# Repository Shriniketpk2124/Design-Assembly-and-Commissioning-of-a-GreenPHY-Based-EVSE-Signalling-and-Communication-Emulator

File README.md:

# Design, Assembly and Commissioning of a GreenPHY-Based EVSE Signalling and Communication Emulator

> **New here?** Start with [the software quickstart](docs/SOFTWARE_QUICKSTART.md) — two ways to fire up the JoSEV SECC (real hardware, or a two-container software simulation).

This repository documents an engineering prototype for EVSE-side control-pilot
(CP) signalling, HomePlug Green PHY communication and ISO 15118 message
observation with a real electric vehicle.

The project combines a custom mixed-signal PCB, an Arduino Nano, a Raspberry
Pi, a Devolo Green PHY modem and a hardware-adapted EcoG `iso15118` SECC.

> [!CAUTION]
> This is a laboratory communication emulator, not a charger. It has no
> authorized high-voltage DC source, verified insulation-monitoring system,
> pre-charge power stage or energy-transfer path. Never connect an HV/DC source
> or use this project to charge a vehicle.

## Demonstrated scope

The validated setup demonstrated:

- IEC 61851 CP generation and feedback monitoring;
- 1 kHz CP PWM, including the 5% HLC duty cycle;
- EV detection through the CP resistor states;
- EVSE-side SLAC using the `plc-utils` `evse` process;
- IPv6 link-local communication and SDP;
- ISO 15118-2 application-message exchange with external payment and no TLS;
- controlled termination before any physical energy transfer.

The final communication experiment used an explicitly enabled, protocol-only
PreCharge probe. It emulated the protocol status needed to pass CableCheck,
reached `PreChargeReq`, rejected the requested voltage/current command and
latched an external STOP. No DC output was produced.

## Repository layout

| Path | Contents |
| --- | --- |
| `hardware/kicad/PWM_Schematic/` | KiCad schematic, PCB, project-local symbols and footprints, and ERC/DRC reports |
| `hardware/bom/` | Bill of materials exported from the final schematic |
| `software/arduino/` | Arduino Nano CP controller and feedback-monitor firmware |
| `software/raspberry-pi/` | Raspberry Pi console, cockpit, test-day and evidence-collection tools |
| `software/josev-modifications/` | Hardware-controller additions for the EcoG ISO 15118 SECC |
| `software/configuration/` | Public configuration templates without local identifiers or secrets |
| `validation/procedures/` | Bench and real-EV validation procedures |
| `validation/selected-results/` | Sanitized results selected for publication |
| `thesis/` | Publication status only; the thesis report is not distributed here |

Raw packet captures, complete run folders, local environment files, vehicle
identifiers and PLC network keys are intentionally excluded.

## System overview

1. The Arduino generates the CP waveform and publishes comparator feedback over
   a serial connection.
2. The Raspberry Pi console is the sole owner of the Arduino serial connection
   and the two CP-path relay GPIOs.
3. The console writes an atomic state snapshot under `/run/evse-monday`.
4. The modified SECC reads that snapshot instead of controlling serial or GPIO
   hardware from inside the container.
5. The `plc-utils` `evse` process is the sole EVSE-side SLAC owner.
6. The Devolo modem carries HomePlug Green PHY traffic between the PCB coupling
   network and the vehicle.
7. The operations script records packet captures, application logs, controller
   state and checksums for each test attempt.

The word **Monday** remains in several tested script, class and configuration
names. It was the internal name of the final real-EV test workflow; it is not a
separate product or protocol.

## Hardware interface

The final KiCad PCB assigns the four-position vehicle-interface terminal as:

| Terminal | Net |
| --- | --- |
| `J2.1` | `EVSE_CP_OUT` |
| `J2.2` | `EVSE_PP_OUT` |
| `J2.3` | `ISO_GND` |
| `J2.4` | Not connected |

Verify these assignments against the supplied schematic and PCB before making
any physical connection. Wiring changes must be performed with all power
removed.

## Software provenance

The Josev modifications were developed against:

- upstream repository: `https://github.com/EcoG-io/iso15118.git`
- recorded base commit: `76bf85be572d16adbcd009a985d605622c3b7227`

The repository contains the project-specific additions and operational files,
not a claim of ownership over the upstream project. Retain all upstream license
and attribution notices when constructing a working tree.

## Replication order

This project is not a one-command charger build. A new user should proceed in
the following order:

1. Read this README and the safety limits.
2. Open `hardware/kicad/PWM_Schematic/PWM_Schematic.kicad_pro` and inspect the
   schematic, PCB, connector assignments and ERC/DRC reports.
3. Review the BOM and confirm every fitted component and polarity against the
   physical assembly.
4. Compile the Arduino sketch in `software/arduino/evse_cp_feedback_led/` for an
   Arduino Nano. The final sketch was verified with Arduino IDE and used 6102
   bytes of program storage and 448 bytes of global SRAM.
5. Prepare a Raspberry Pi with Docker Compose, Python 3, `tmux`, `tcpdump`,
   `plc-utils` and the required GPIO/serial permissions.
6. Follow the [Raspberry Pi installation and first-start guide](software/raspberry-pi/README.md)
   to check out the recorded upstream `iso15118` revision, prepare the local
   configuration and install the project additions.
7. Copy the public templates from `software/configuration/` to local,
   git-ignored configuration files and replace every `CHANGE_ME` value.
8. Run the hardware-independent tests and the operations-script preflight.
9. Validate State A, State B and 5% HLC feedback using bench loads before a
   vehicle is connected.
10. Only after the bench checks pass, follow the hardware-specific procedure in
    `validation/procedures/REAL_EV_COMMUNICATION_TEST_RUNBOOK.md`.

## Operating modes

`MONDAY_PRECHARGE_PROBE` materially changes the protocol boundary:

| Value | Behaviour |
| --- | --- |
| `0` | Default fail-safe mode. Reports `No_IMD`/`EVSE_NotReady` and requests STOP when CableCheck cannot be truthfully completed. |
| `1` | Test-only protocol probe. Emulates CableCheck readiness to observe entry into PreCharge, but still blocks the requested charging command and requests STOP. |

The probe does not add an IMD, contactor, pre-charge circuit or voltage source.
Do not enable it on a system containing an HV/DC energy path.

## Evidence and privacy

Complete test archives can contain MAC addresses, PLC network keys, EVCC
identifiers, hostnames, operator names and packet payloads. They are private
laboratory evidence and are not suitable for direct publication. Publish only
purpose-selected, sanitized extracts.

## Project status

The repository captures a thesis prototype and its validated laboratory
workflow. It is intended for research, review and reproducibility work by
qualified users. It is not production EVSE firmware and has not been certified
for charging, electrical safety or standards conformance.

The thesis report is withheld until publication permission is confirmed.

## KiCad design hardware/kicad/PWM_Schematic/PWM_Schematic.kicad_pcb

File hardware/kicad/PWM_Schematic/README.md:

\# PWM and Control-Pilot PCB

This directory contains the KiCad source files for the mixed-signal PCB used by

the Green PHY EVSE signalling and communication emulator.

\## Requirements

\- KiCad 10

\- Standard KiCad symbol libraries

\- Standard KiCad footprint libraries

\- Standard KiCad 3D-model package, if 3D rendering is required

\## Opening the project

Open:

`PWM\_Schematic.kicad\_pro`

The custom symbol and footprint libraries required by the project are included

locally in the `symbols/` and `footprints/` directories. The corresponding

`sym-lib-table` and `fp-lib-table` files use `${KIPRJMOD}` paths, so the project

does not depend on machine-specific directories.

\## Included source files

\- `PWM\_Schematic.kicad\_pro` — KiCad project settings

\- `PWM\_Schematic.kicad\_sch` — schematic

\- `PWM\_Schematic.kicad\_pcb` — PCB layout

\- `PWM\_Schematic.kicad\_dru` — custom design rules

\- `symbols/` — project-local custom symbols

\- `footprints/` — project-local custom footprints

\- `reports/` — final ERC and DRC reports

\## Verification status

Final verification performed on 2026-10-04:

\- ERC errors: 0

\- ERC warnings: 0

\- DRC violations: 0

\- Unconnected pads: 0

\- Footprint errors: 0

The corresponding reports are stored in `reports/`.

\## 3D models

Standard components use the official KiCad 10 3D-model library where available.

Nonportable or incorrect custom 3D-model references were removed. Missing custom

3D models do not affect schematic connectivity, PCB routing, fabrication output

or design-rule verification.

\## Fabrication outputs

Historical Gerber and Aisler exports are not included because they predate the

final DRC-clean source revision. Fabrication outputs should be regenerated from

the checked PCB source when required.

\## Scope and safety

This PCB is a research prototype for control-pilot signalling, proximity-pilot

interfacing and communication-layer experimentation. It is not a certified EVSE

power stage and must not be treated as authorization for high-voltage or energy

transfer.

\## Third-party library data

Some project-local symbol and footprint definitions originated from manufacturer

or electronic-library-loader data and were adapted for this project. Applicable

redistribution terms must be reviewed before making the repository public.

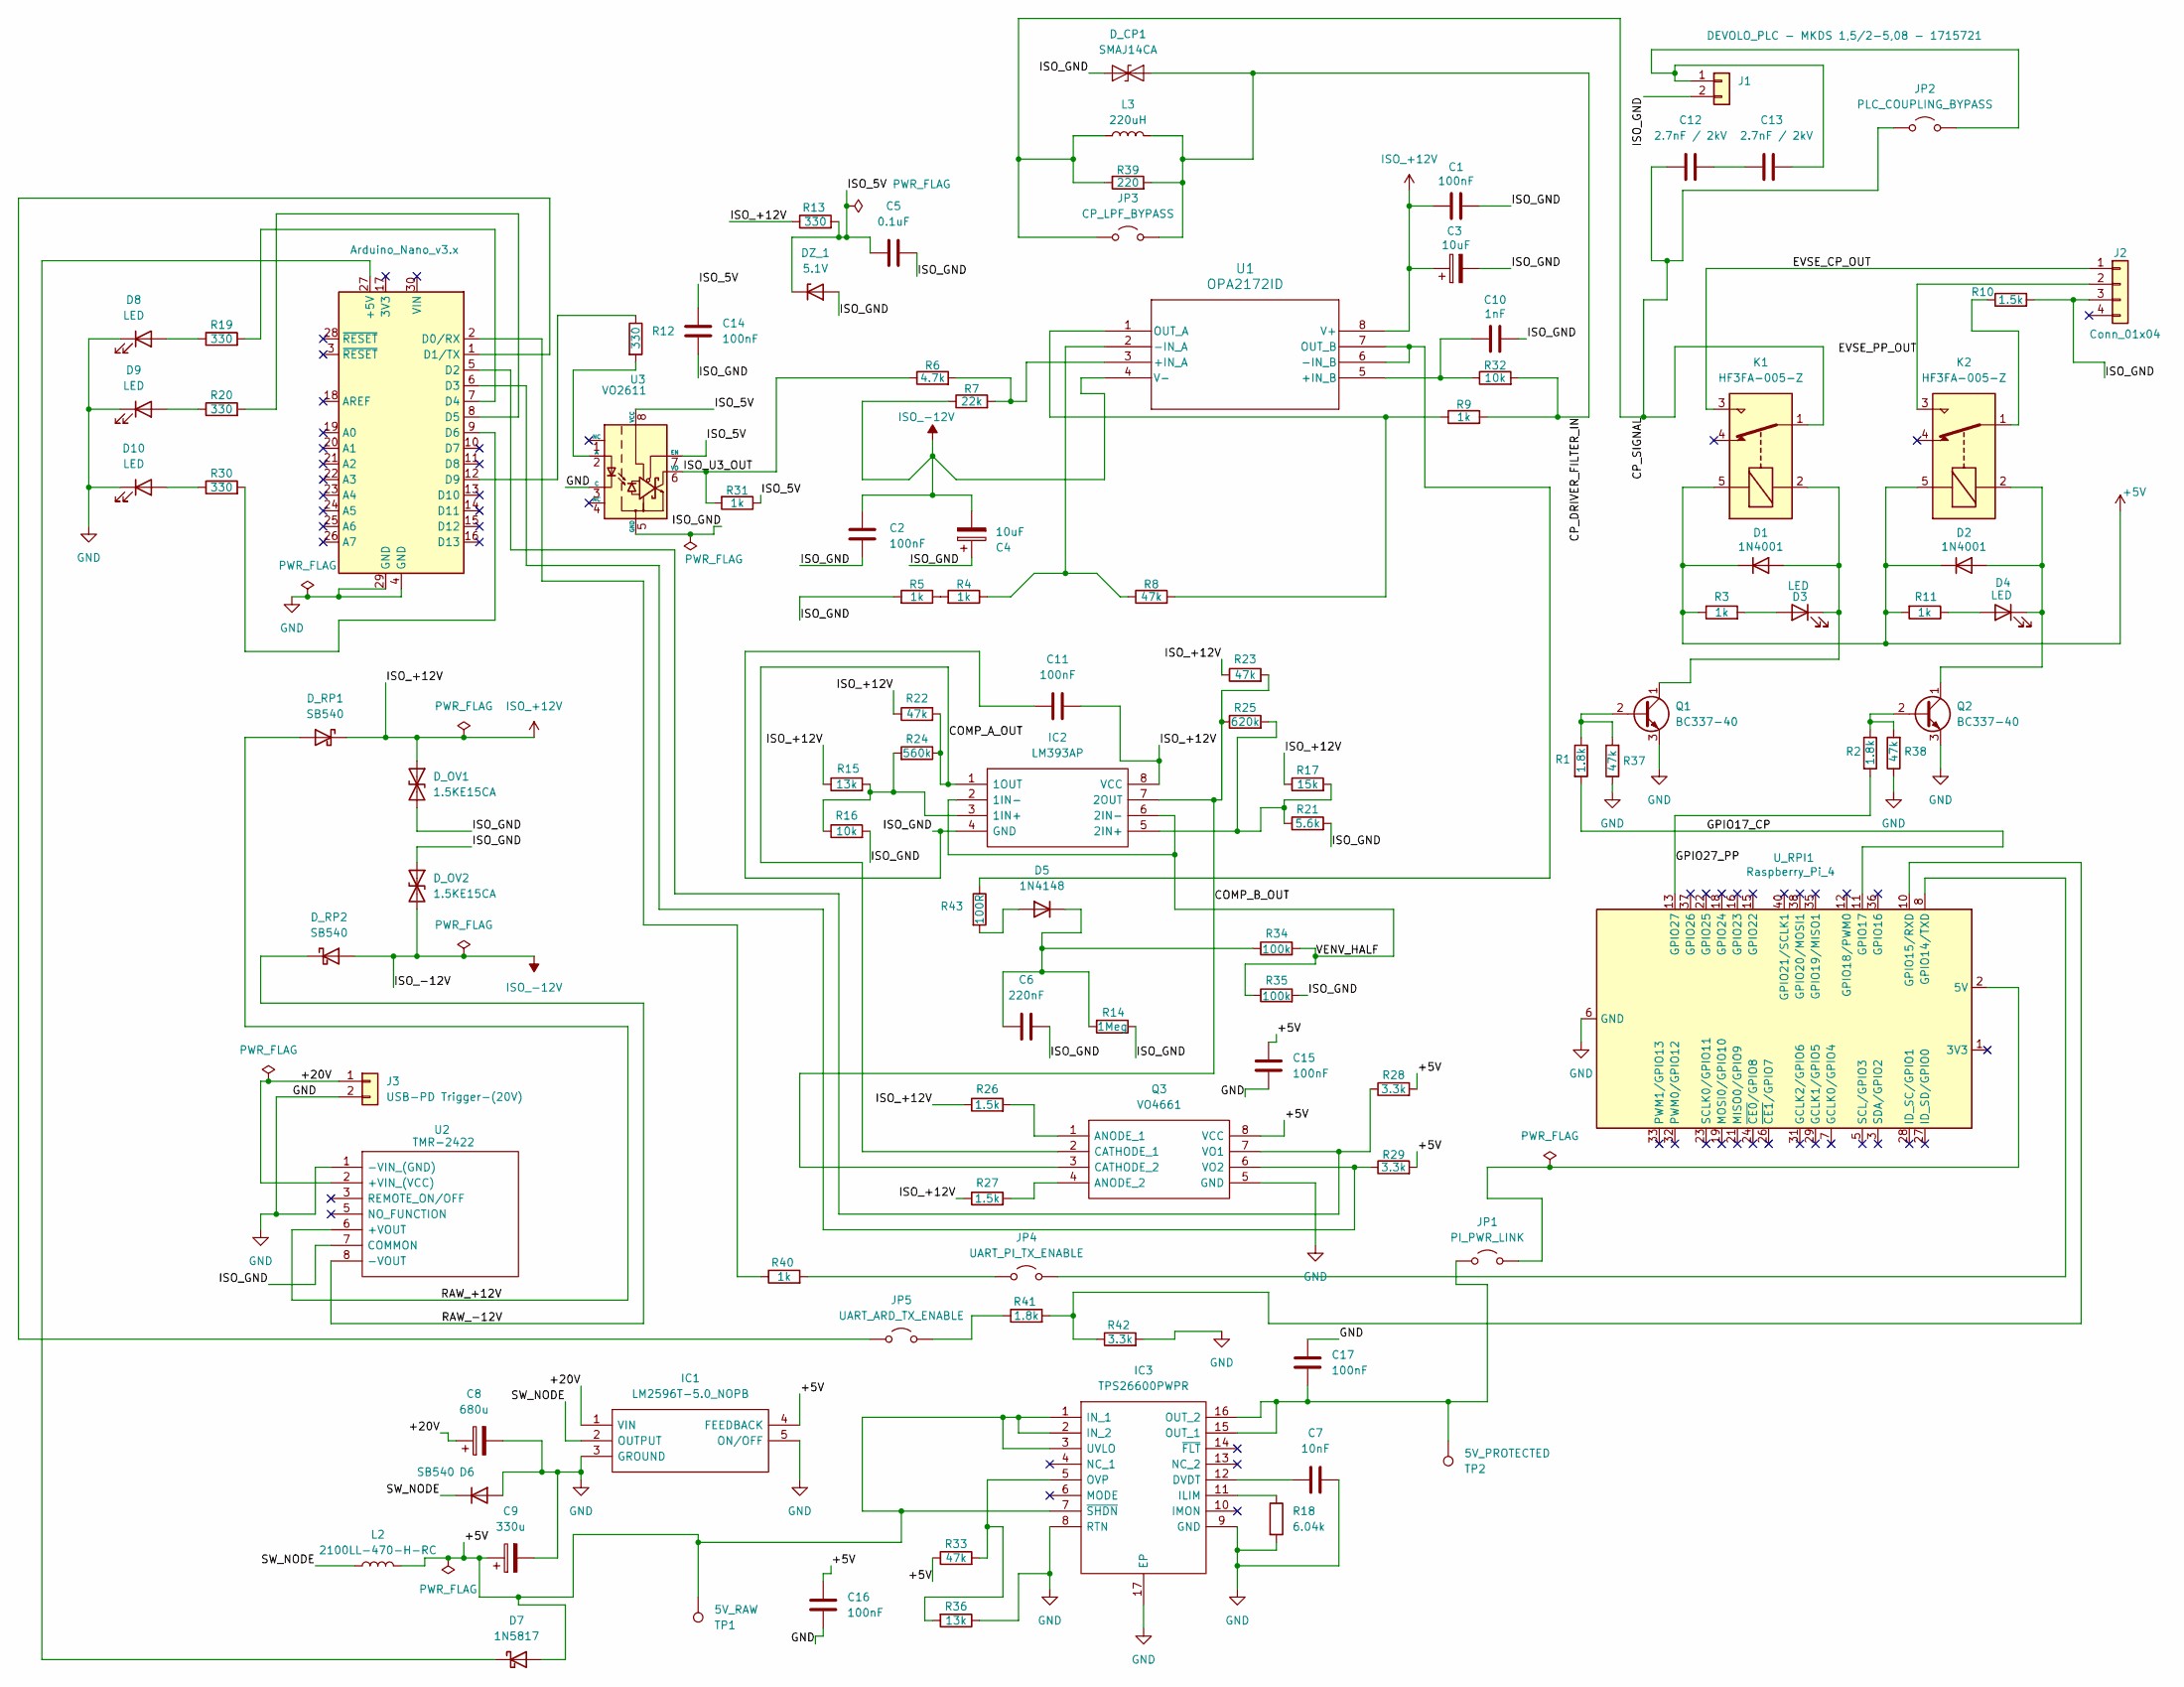
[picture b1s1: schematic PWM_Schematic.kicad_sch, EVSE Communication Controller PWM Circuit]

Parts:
A1: Arduino_Nano_v3.x; Arduino_Nano
C1, C2, C11, C14, C15: 100nF; C_Disc_D5.0mm_W2.5mm_P2.50mm
C3, C4: 10uF; CP_Radial_D5.0mm_P2.00mm
C5: 0.1uF; C_Disc_D5.0mm_W2.5mm_P2.50mm
C6: 220nF; C_Universal_P2.54_L5.5_W3.5
C7: 10nF; C_Disc_D5.0mm_W2.5mm_P2.50mm
C8: 680u; CP_Radial_D12.5mm_P5.00mm
C9: 330u; CP_Radial_D10.0mm_P5.00mm
C10: 1nF; C_Disc_D5.0mm_W2.5mm_P2.50mm
C12, C13: 2.7nF / 2kV; C_Rect_L18.0mm_W5.0mm_P15.00mm_FKS3_FKP3; MPN R75UI127050H4J
C16, C17: 100nF; C_0805_2012Metric
D1, D2: 1N4001; D_DO-41_SOD81_P7.62mm_Horizontal
D3, D4, D8, D9, D10: LED; LED_D5.0mm
D5: 1N4148; D_DO-35_SOD27_P7.62mm_Horizontal
D6: SB540; D_DO-201AD_P15.24mm_Horizontal
D7: 1N5817; D_DO-41_SOD81_P7.62mm_Horizontal
DZ_1: 5.1V; D_DO-35_SOD27_P7.62mm_Horizontal
D_CP1: SMAJ14CA; D_SMA; MPN SMAJ14CA
D_OV1, D_OV2: 1.5KE15CA; D_DO-201AD_P15.24mm_Horizontal
D_RP1, D_RP2: SB540; D_DO-201AD_P15.24mm_Horizontal
IC1: LM2596T-5.0_NOPB; TO170P470X1028X2117-5P; Mouser Part Number 926-LM2596T-5.0/NOPB
IC2: LM393AP; LM393_DIP8_AISLER_0p30mm_Annular; Mouser Part Number 595-LM393P
IC3: TPS26600PWPR; HTSSOP-16-1EP_4.4x5mm_P0.65mm_EP3x3mm; Mouser Part Number 595-TPS26600PWPR
J1: DEVOLO_PLC - MKDS 1,5/2-5,08 - 1715721; TerminalBlock_Universal_1x02_P5.08_Phoenix_Molex
J2: Conn_01x04; TerminalBlock_Phoenix_MPT-0,5-4-2.54_1x04_P2.54mm_Horizontal
J3: USB-PD Trigger-(20V); PinSocket_1x02_P2.54mm_Vertical
JP1: PI_PWR_LINK; PinHeader_1x02_P2.54mm_Vertical
JP2: PLC_COUPLING_BYPASS; PinHeader_1x02_P2.54mm_Vertical
JP3: CP_LPF_BYPASS; PinHeader_1x02_P2.54mm_Vertical
JP4: UART_PI_TX_ENABLE; PinHeader_1x02_P2.54mm_Vertical
JP5: UART_ARD_TX_ENABLE; PinHeader_1x02_P2.54mm_Vertical
K1: HF3FA-005-Z; Relay_SPDT_SANYOU_SRD_Series_Form_C Modified_1
K2: HF3FA-005-Z; Relay_SPDT_SANYOU_SRD_Series_Form_C_Modified
L2: 2100LL-470-H-RC; L2_AISLER_0p30mm_Annular
L3: 220uH; L_Wurth_7447020_P7.00mm_1; MPN 7447020
Q1, Q2: BC337-40; TO-92_Inline_Wide
Q3: VO4661; VO4661_DIP8_AISLER_0p30mm_Annular; Mouser Part Number 782-VO4661
R1, R2, R41: 1.8k; R_Axial_DIN0207_L6.3mm_D2.5mm_P7.62mm_Horizontal
R3, R4, R5, R9, R11, R31, R40: 1k; R_Axial_DIN0207_L6.3mm_D2.5mm_P7.62mm_Horizontal
R6: 4.7k; R_Axial_DIN0207_L6.3mm_D2.5mm_P7.62mm_Horizontal
R7: 22k; R_Axial_DIN0207_L6.3mm_D2.5mm_P7.62mm_Horizontal
R8, R22, R23, R33, R37, R38: 47k; R_Axial_DIN0207_L6.3mm_D2.5mm_P7.62mm_Horizontal
R10, R26, R27: 1.5k; R_Axial_DIN0207_L6.3mm_D2.5mm_P7.62mm_Horizontal
R12, R13, R19, R20, R30: 330; R_Axial_DIN0207_L6.3mm_D2.5mm_P7.62mm_Horizontal
R14: 1Meg; R_Axial_DIN0207_L6.3mm_D2.5mm_P7.62mm_Horizontal
R15, R36: 13k; R_Axial_DIN0207_L6.3mm_D2.5mm_P7.62mm_Horizontal
R16, R32: 10k; R_Axial_DIN0207_L6.3mm_D2.5mm_P7.62mm_Horizontal
R17: 15k; R_Axial_DIN0207_L6.3mm_D2.5mm_P7.62mm_Horizontal
R18: 6.04k; R_Axial_DIN0207_L6.3mm_D2.5mm_P7.62mm_Horizontal
R21: 5.6k; R_Axial_DIN0207_L6.3mm_D2.5mm_P7.62mm_Horizontal
R24: 560k; R_Axial_DIN0207_L6.3mm_D2.5mm_P7.62mm_Horizontal
R25: 620k; R_Axial_DIN0207_L6.3mm_D2.5mm_P7.62mm_Horizontal
R28, R29, R42: 3.3k; R_Axial_DIN0207_L6.3mm_D2.5mm_P7.62mm_Horizontal
R34, R35: 100k; R_Axial_DIN0207_L6.3mm_D2.5mm_P7.62mm_Horizontal
R39: 220; R_Axial_DIN0207_L6.3mm_D2.5mm_P7.62mm_Horizontal
R43: 100R; R_Axial_DIN0207_L6.3mm_D2.5mm_P7.62mm_Horizontal
TP1: 5V_RAW; TestPoint_THTPad_D2.0mm_Drill1.0mm
TP2: 5V_PROTECTED; TestPoint_THTPad_D2.0mm_Drill1.0mm
U1: OPA2172ID; D8_TEX
U2: TMR-2422; Converter_DCDC_TRACO_TEC2-12xxWI_24xxWI_48xxWI_THT; Mouser Part Number 495-TMR-2422
U3: VO2611; DIP-8_W7.62mm
U_RPI1: Raspberry_Pi_4; PinSocket_2x20_P2.54mm_Vertical

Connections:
+5V: C9.1, C15.1, C16.1, D1.1 (K), D2.1 (K), D7.2 (A), IC1.4 (FEEDBACK), IC3.1 (IN_1), IC3.2 (IN_2), IC3.3 (UVLO), IC3.7 (~SHDN), K1.5, K2.5, L2.2, Q3.8 (VCC), R3.1, R11.2, R28.2, R29.2, R33.1, TP1.1 (1_1)
/+20V: C8.1, IC1.1 (VIN), J3.1, U2.2 (+VIN_(VCC))
/COMP_A_OUT: IC2.1 (1OUT), Q3.2 (CATHODE_1), R22.2, R24.1
/COMP_B_OUT: IC2.7 (2OUT), Q3.3 (CATHODE_2), R23.2, R25.1
/CP_DRIVER_FILTER_IN: D_CP1.2 (A2), JP3.2 (B), L3.2, R9.2, R32.2, R39.2
/CP_SIGNAL: C12.1, JP2.1 (A), JP3.1 (A), K1.1, L3.1, R39.1
/EVSE_CP_OUT: J2.1, K1.3
/EVSE_PP_OUT: J2.2, K2.3
/GPIO17_CP: R1.2, U_RPI1.11 (GPIO17)
/GPIO27_PP: R2.2, U_RPI1.13 (GPIO27)
/ISO_5V: C5.1, C14.1, DZ_1.1 (K), R13.2, R31.1, U3.7 (EN), U3.8 (VCC)
/ISO_GND: C1.1, C2.2, C3.2, C4.1, C5.2, C6.2, C10.2, C11.1, C14.2, DZ_1.2 (A), D_CP1.1 (A1), D_OV1.2 (A2), D_OV2.1 (A1), IC2.4 (GND), J1.2, J2.3, R5.2, R10.2, R14.1, R16.2, R21.2, R35.2, U2.7 (COMMON), U3.5 (GND)
/ISO_U3_OUT: R6.1, R31.2, U3.6 (VO)
/RAW_+12V: D_RP1.2 (A), U2.6 (+VOUT)
/RAW_-12V: D_RP2.1 (K), U2.8 (-VOUT)
/SW_NODE: D6.1 (K), IC1.2 (OUTPUT), L2.1
/VENV_HALF: IC2.2 (1IN-), IC2.6 (2IN-), R34.2, R35.1
GND: A1.4 (GND), A1.29 (GND), C7.2, C8.2, C9.2, C15.2, C16.2, C17.1, D6.2 (A), D8.1 (K), D9.1 (K), D10.1 (K), IC1.3 (GROUND), IC1.5 (ON/OFF), IC3.8 (RTN), IC3.9 (GND), IC3.17 (EP), J3.2, Q1.3 (E), Q2.3 (E), Q3.5 (GND), R18.2, R36.1, R37.1, R38.1, R42.2, U2.1 (-VIN_(GND)), U3.3 (C), U_RPI1.6 (GND), U_RPI1.9 (GND), U_RPI1.14 (GND), U_RPI1.20 (GND), U_RPI1.25 (GND), U_RPI1.30 (GND), U_RPI1.34 (GND), U_RPI1.39 (GND)
ISO_+12V: C1.2, C3.1, C11.2, D_OV1.1 (A1), D_RP1.1 (K), IC2.8 (VCC), R13.1, R15.1, R17.1, R22.1, R23.1, R26.1, R27.1, U1.8 (V+)
ISO_-12V: C2.1, C4.2, D_OV2.2 (A2), D_RP2.2 (A), R7.1, U1.4 (V-)
unnamed: A1.27 (+5V), D7.1 (K)
unnamed: A1.2 (D0/RX), R40.1
unnamed: A1.1 (D1/TX), JP5.1 (A)
unnamed: A1.5 (D2), Q3.7 (VO1), R28.1
unnamed: A1.6 (D3), Q3.6 (VO2), R29.1
unnamed: A1.7 (D4), R19.2
unnamed: A1.8 (D5), R20.2
unnamed: A1.9 (D6), R30.2
unnamed: A1.12 (D9), R12.1
unnamed: C12.2, C13.1
unnamed: D1.2 (A), D3.1 (K), K1.2, Q1.1 (C)
unnamed: D2.2 (A), D4.1 (K), K2.2, Q2.1 (C)
unnamed: D3.2 (A), R3.2
unnamed: D4.2 (A), R11.1
unnamed: D5.2 (A), R43.2
unnamed: C6.1, D5.1 (K), R14.2, R34.1
unnamed: D8.2 (A), R19.1
unnamed: D9.2 (A), R20.1
unnamed: D10.2 (A), R30.1
unnamed: IC2.3 (1IN+), R15.2, R16.1, R24.2
unnamed: IC2.5 (2IN+), R17.2, R21.1, R25.2
unnamed: C7.1, IC3.12 (DVDT)
unnamed: IC3.11 (ILIM), R18.1
unnamed: C17.2, IC3.15 (OUT_1), IC3.16 (OUT_2), JP1.1 (A), TP2.1 (1_1)
unnamed: IC3.5 (OVP), R33.2, R36.2
unnamed: C13.2, J1.1, JP2.2 (B)
unnamed: JP1.2 (B), U_RPI1.2 (5V), U_RPI1.4 (5V)
unnamed: JP4.1 (A), R40.2
unnamed: JP4.2 (B), U_RPI1.8 (GPIO14/TXD)
unnamed: JP5.2 (B), R41.1
unnamed: K2.1, R10.1
unnamed: Q1.2 (B), R1.1, R37.2
unnamed: Q2.2 (B), R2.1, R38.2
unnamed: Q3.1 (ANODE_1), R26.2
unnamed: Q3.4 (ANODE_2), R27.2
unnamed: R4.2, R5.1
unnamed: R6.2, R7.2, U1.3 (+IN_A)
unnamed: C10.1, R32.1, U1.5 (+IN_B)
unnamed: R4.1, R8.1, U1.2 (-IN_A)
unnamed: R43.1, U1.6 (-IN_B), U1.7 (OUT_B)
unnamed: R8.2, R9.1, U1.1 (OUT_A)
unnamed: R12.2, U3.2 (A)
unnamed: R41.2, R42.1, U_RPI1.10 (GPIO15/RXD)

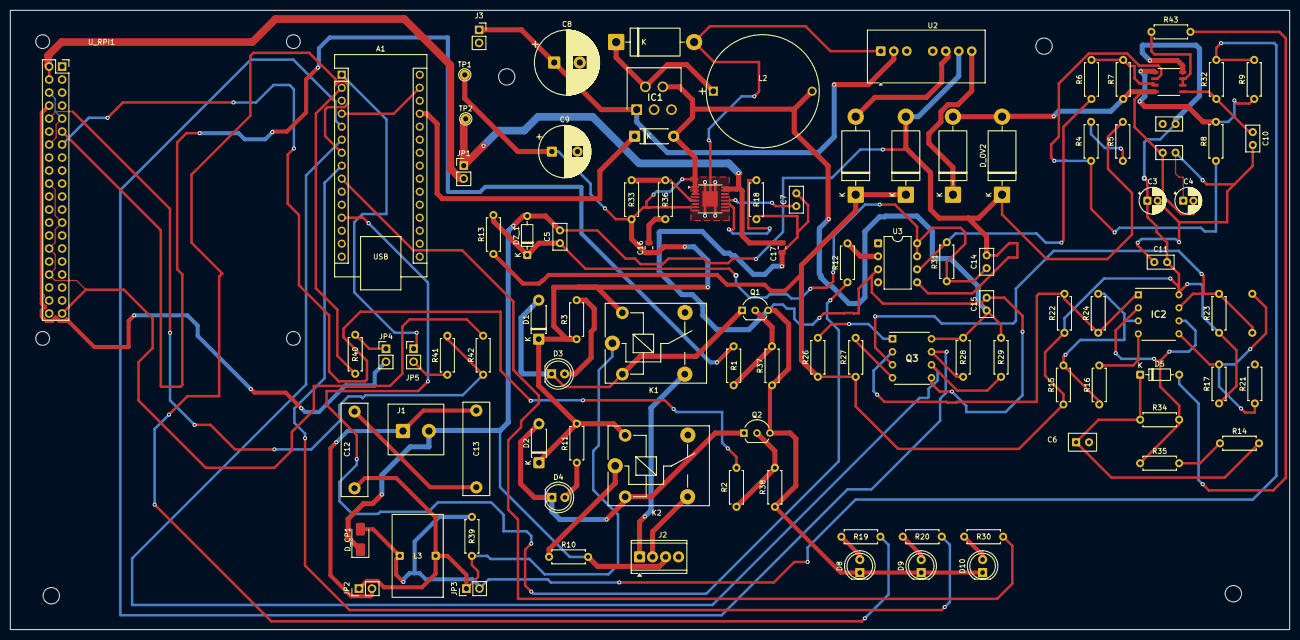
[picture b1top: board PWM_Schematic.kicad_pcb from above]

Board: 2 copper layers, 250.0 x 121.0 mm, 101 parts (1 on the bottom side), 63 nets.

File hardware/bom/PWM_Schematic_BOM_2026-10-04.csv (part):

"Reference","Value","Footprint","Qty","Description","Datasheet","#"
"A1","Arduino_Nano_v3.x","Module:Arduino_Nano","1","Arduino Nano v3.x","http://www.mouser.com/pdfdocs/Gravitech_Arduino_Nano3_0.pdf","1"
"C1,C2,C11,C14,C15","100nF","Capacitor_THT:C_Disc_D5.0mm_W2.5mm_P2.50mm","5","Unpolarized capacitor","","2"
"C3,C4","10uF","Capacitor_THT:CP_Radial_D5.0mm_P2.00mm","2","Polarized capacitor","","3"
"C5","0.1uF","Capacitor_THT:C_Disc_D5.0mm_W2.5mm_P2.50mm","1","Unpolarized capacitor","","4"
"C6","220nF","PWM_Schematic:C_Universal_P2.54_L5.5_W3.5","1","Unpolarized capacitor","","5"
"C7","10nF","Capacitor_THT:C_Disc_D5.0mm_W2.5mm_P2.50mm","1","Unpolarized capacitor","","6"
"C8","680u","Capacitor_THT:CP_Radial_D12.5mm_P5.00mm","1","Polarized capacitor","","7"
"C9","330u","Capacitor_THT:CP_Radial_D10.0mm_P5.00mm","1","Polarized capacitor","","8"
"C10","1nF","Capacitor_THT:C_Disc_D5.0mm_W2.5mm_P2.50mm","1","Unpolarized capacitor","","9"
"C12,C13","2.7nF / 2kV","Capacitor_THT:C_Rect_L18.0mm_W5.0mm_P15.00mm_FKS3_FKP3","2","2.7 nF, 2 kV, ±5%, polypropylene film capacitor, THT, 15 mm pitch","","10"
"C16,C17","100nF","Capacitor_SMD:C_0805_2012Metric","2","Unpolarized capacitor","","11"
"D1,D2","1N4001","Diode_THT:D_DO-41_SOD81_P7.62mm_Horizontal","2","Diode","","12"
"D3,D4,D8,D9,D10","LED","LED_THT:LED_D5.0mm","5","Light emitting diode","","13"
"D5","1N4148","Diode_THT:D_DO-35_SOD27_P7.62mm_Horizontal","1","Diode","","14"
"D6","SB540","Diode_THT:D_DO-201AD_P15.24mm_Horizontal","1","Diode","","15"
"D7","1N5817","Diode_THT:D_DO-41_SOD81_P7.62mm_Horizontal","1","Schottky diode","","16"
"DZ_1","5.1V","Diode_THT:D_DO-35_SOD27_P7.62mm_Horizontal","1","Zener diode","","17"
"D_CP1","SMAJ14CA","Diode_SMD:D_SMA","1","400W bidirectional Transient Voltage Suppressor, 14.0Vr, SMA(DO-214AC)","https://www.littelfuse.com/media?resourcetype=datasheets&ite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","18"
"D_OV1,D_OV2","1.5KE15CA","Diode_THT:D_DO-201AD_P15.24mm_Horizontal","2","Bidirectional transient-voltage-suppression diode","","19"
"D_RP1,D_RP2","SB540","Diode_THT:D_DO-201AD_P15.24mm_Horizontal","2","Schottky diode","","20"
"IC1","LM2596T-5.0_NOPB","PWM_Schematic_Custom:TO170P470X1028X2117-5P","1","SIMPLE SWITCHER&#174; 4.5V to 40V, 3A Low Component Count Step-Down Regulator","http://www.ti.com/lit/gpn/lm2596","21"
"IC2","LM393AP","PWM_Schematic_Custom:LM393_DIP8_AISLER_0p30mm_Annular","1","LM393P, Dual Comparator Open Collector 1.3us 12 V, 15 V, 18 V, 24 V, 28 V, 3 V, 5 V, 9 V 8-Pin PDIP","http://www.ti.com/lit/ds/symlink/lm393.pdf","22"
"IC3","TPS26600PWPR","Package_SO:HTSSOP-16-1EP_4.4x5mm_P0.65mm_EP3x3mm","1","60V 2A Industrial eFuse With Integrated Reverse-Input Polarity Protection","http://www.ti.com/lit/gpn/tps2660","23"
"J1","DEVOLO_PLC - MKDS 1,5/2-5,08 - 1715721","PWM_Schematic:TerminalBlock_Universal_1x02_P5.08_Phoenix_Molex","1","Generic connector, single row, 01x02, script generated (kicad-library-utils/schlib/autogen/connector/)","","24"
"J2","Conn_01x04","TerminalBlock_Phoenix:TerminalBlock_Phoenix_MPT-0,5-4-2.54_1x04_P2.54mm_Horizontal","1","Generic connector, single row, 01x04, script generated (kicad-library-utils/schlib/autogen/connector/)","","25"
"J3","USB-PD Trigger-(20V)","Connector_PinSocket_2.54mm:PinSocket_1x02_P2.54mm_Vertical","1","Generic connector, single row, 01x02, script generated (kicad-library-utils/schlib/autogen/connector/)","","26"
"JP1","PI_PWR_LINK","Connector_PinHeader_2.54mm:PinHeader_1x02_P2.54mm_Vertical","1","Jumper, 2-pole, open","","27"
"JP2","PLC_COUPLING_BYPASS","Connector_PinHeader_2.54mm:PinHeader_1x02_P2.54mm_Vertical","1","Jumper, 2-pole, open","","28"
"JP3","CP_LPF_BYPASS","Connector_PinHeader_2.54mm:PinHeader_1x02_P2.54mm_Vertical","1","Jumper, 2-pole, open","","29"
"JP4","UART_PI_TX_ENABLE","Connector_PinHeader_2.54mm:PinHeader_1x02_P2.54mm_Vertical","1","Jumper, 2-pole, open","","30"
"JP5","UART_ARD_TX_ENABLE","Connector_PinHeader_2.54mm:PinHeader_1x02_P2.54mm_Vertical","1","Jumper, 2-pole, open","","31"
"K1","HF3FA-005-Z","PWM_Schematic_Custom:Relay_SPDT_SANYOU_SRD_Series_Form_C Modified_1","1","","http://www.sanyourelay.ca/public/products/pdf/SRD.pdf","32"
"K2","HF3FA-005-Z","PWM_Schematic_Custom:Relay_SPDT_SANYOU_SRD_Series_Form_C_Modified","1","","http://www.sanyourelay.ca/public/products/pdf/SRD.pdf","33"
"L2","2100LL-470-H-RC","PWM_Schematic_Custom:L2_AISLER_0p30mm_Annular","1","Inductor","","34"
"L3","220uH","PWM_Schematic:L_Wurth_7447020_P7.00mm_1","1","Inductor","","35"
"Q1,Q2","BC337-40","Package_TO_SOT_THT:TO-92_Inline_Wide","2","0.8A Ic, 45V Vce, NPN Transistor, TO-92","https://diotec.com/tl_files/diotec/files/pdf/datasheets/bc337.pdf","36"
"Q3","VO4661","PWM_Schematic_Custom:VO4661_DIP8_AISLER_0p30mm_Annular","1","Logic Output Optoisolator 10MBd Open Drain 5300Vrms 2 Channel 15kV/s CMTI 8-DIP","https://www.vishay.com/docs/80412/vo2630_vo2631_vo4661.pdf","37"
"R1,R2,R41","1.8k","Resistor_THT:R_Axial_DIN0207_L6.3mm_D2.5mm_P7.62mm_Horizontal","3","Resistor","","38"
"R3,R11,R31,R40","1k","Resistor_THT:R_Axial_DIN0207_L6.3mm_D2.5mm_P7.62mm_Horizontal","4","Resistor","","39"
"R4,R5,R9","1k","Resistor_THT:R_Axial_DIN0207_L6.3mm_D2.5mm_P7.62mm_Horizontal","3","","","40"
"R6","4.7k","Resistor_THT:R_Axial_DIN0207_L6.3mm_D2.5mm_P7.62mm_Horizontal","1","","","41"
"R7","22k","Resistor_THT:R_Axial_DIN0207_L6.3mm_D2.5mm_P7.62mm_Horizontal","1","","","42"
"R8","47k","Resistor_THT:R_Axial_DIN0207_L6.3mm_D2.5mm_P7.62mm_Horizontal","1","","","43"
"R10","1.5k","Resistor_THT:R_Axial_DIN0207_L6.3mm_D2.5mm_P7.62mm_Horizontal","1","","","44"
"R12,R13,R19,R20,R30","330","Resistor_THT:R_Axial_DIN0207_L6.3mm_D2.5mm_P7.62mm_Horizontal","5","Resistor","","45"
"R14","1Meg","Resistor_THT:R_Axial_DIN0207_L6.3mm_D2.5mm_P7.62mm_Horizontal","1","Resistor","","46"
"R15,R36","13k","Resistor_THT:R_Axial_DIN0207_L6.3mm_D2.5mm_P7.62mm_Horizontal","2","Resistor","","47"
"R16,R32","10k","Resistor_THT:R_Axial_DIN0207_L6.3mm_D2.5mm_P7.62mm_Horizontal","2","Resistor","","48"
"R17","15k","Resistor_THT:R_Axial_DIN0207_L6.3mm_D2.5mm_P7.62mm_Horizontal","1","Resistor","","49"
"R18","6.04k","Resistor_THT:R_Axial_DIN0207_L6.3mm_D2.5mm_P7.62mm_Horizontal","1","Resistor","","50"
"R21","5.6k","Resistor_THT:R_Axial_DIN0207_L6.3mm_D2.5mm_P7.62mm_Horizontal","1","Resistor","","51"
"R22,R23,R33,R37,R38","47k","Resistor_THT:R_Axial_DIN0207_L6.3mm_D2.5mm_P7.62mm_Horizontal","5","Resistor","","52"
"R24","560k","Resistor_THT:R_Axial_DIN0207_L6.3mm_D2.5mm_P7.62mm_Horizontal","1","Resistor","","53"
"R25","620k","Resistor_THT:R_Axial_DIN0207_L6.3mm_D2.5mm_P7.62mm_Horizontal","1","Resistor","","54"
"R26,R27","1.5k","Resistor_THT:R_Axial_DIN0207_L6.3mm_D2.5mm_P7.62mm_Horizontal","2","Resistor","","55"
"R28,R29,R42","3.3k","Resistor_THT:R_Axial_DIN0207_L6.3mm_D2.5mm_P7.62mm_Horizontal","3","Resistor","","56"
"R34,R35","100k","Resistor_THT:R_Axial_DIN0207_L6.3mm_D2.5mm_P7.62mm_Horizontal","2","Resistor","","57"
"R39","220","Resistor_THT:R_Axial_DIN0207_L6.3mm_D2.5mm_P7.62mm_Horizontal","1","Resistor","","58"
"R43","100R","Resistor_THT:R_Axial_DIN0207_L6.3mm_D2.5mm_P7.62mm_Horizontal","1","Resistor","","59"
"TP1","5V_RAW","TestPoint:TestPoint_THTPad_D2.0mm_Drill1.0mm","1","test point","","60"
"TP2","5V_PROTECTED","TestPoint:TestPoint_THTPad_D2.0mm_Drill1.0mm","1","test point","","61"
"U1","OPA2172ID","TLV2172IDR_SOIC8:D8_TEX","1","","https://www.ti.com/lit/gpn/tlv2172","62"
"U2","TMR-2422","Converter_DCDC:Converter_DCDC_TRACO_TEC2-12xxWI_24xxWI_48xxWI_THT","1","2 Watt DC/DC converter, industrial, 2:1 input, regulated, 1600 VDC I/O-isolation, encapsulated, SIP-8","https://tracopower.com/tmr2-datasheet/","63"
"U3","VO2611","Package_DIP:DIP-8_W7.62mm","1","Single High Speed LSTTL/TTL Compatible Optocoupler with enable, dV/dt 1000/us, VCM 10, max 7V VCC, DIP-8","https://www.vishay.com/docs/84732/6n137_vo2601_vo2611.pdf","64"
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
